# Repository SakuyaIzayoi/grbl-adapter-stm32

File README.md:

# grbl-adapter-stm32
GRBL Adapter using an STM32 BluePill

### Stepcraft D600 GRBL Settings
| Setting | Value | Description |
| --- | --- | --- |
| $0 | 50 | Step pulse time |
| $1 | 100 | Step idle delay |
| $2 | 0 | Step pulse invert |
| $3 | 0 | Step direction invert |
| $4 | 1 | Invert step enable pin |
| $5 | 1 | Invert limit pins |
| $6 | 1 | Invert probe pin |
| $10 | 1 | Status report options |
| $11 | 0.010 | Junction deviation |
| $13 | 0 | Report in inches |
| $20 | 1 | Soft limits enable |
| $21 | 1 | Hard limits enable |
| $22 | 1 | Homing cycle enable |
| $23 | 1 | Homing direction invert |
| $24 | 120.000 | Homing locate feed rate |
| $25 | 900.000 | Homing search seek rate |
| $26 | 250 | Homing switch debounce delay |
| $27 | 1.000 | Homing switch pull-off distance |
| $30 | 1000 | Maximum spindle speed |
| $31 | 0 | Minimum spindle speed |
| $32 | 0 | Laser-mode enable |
| $100 | 133.333 | X-ais travel resolution |
| $101 | 133.333 | Y-ais travel resolution |
| $102 | 133.333 | Z-ais travel resolution |
| $103 | 133.333 | A-ais travel resolution |
| $110 | 800.000 | X-axis maximum rate |
| $111 | 800.000 | Y-axis maximum rate |
| $112 | 800.000 | Z-axis maximum rate |
| $113 | 800.000 | A-axis maximum rate |
| $120 | 5.000 | X-axis acceleration |
| $121 | 5.000 | Y-axis acceleration |
| $122 | 5.000 | Z-axis acceleration |
| $123 | 5.000 | A-axis acceleration |
| $130 | 300.000 | X-axis maximum travel |
| $131 | 420.000 | Y-axis maximum travel |
| $132 | 140.000 | Z-axis maximum travel |
| $133 | 100.000 | A-axis maximum travel |

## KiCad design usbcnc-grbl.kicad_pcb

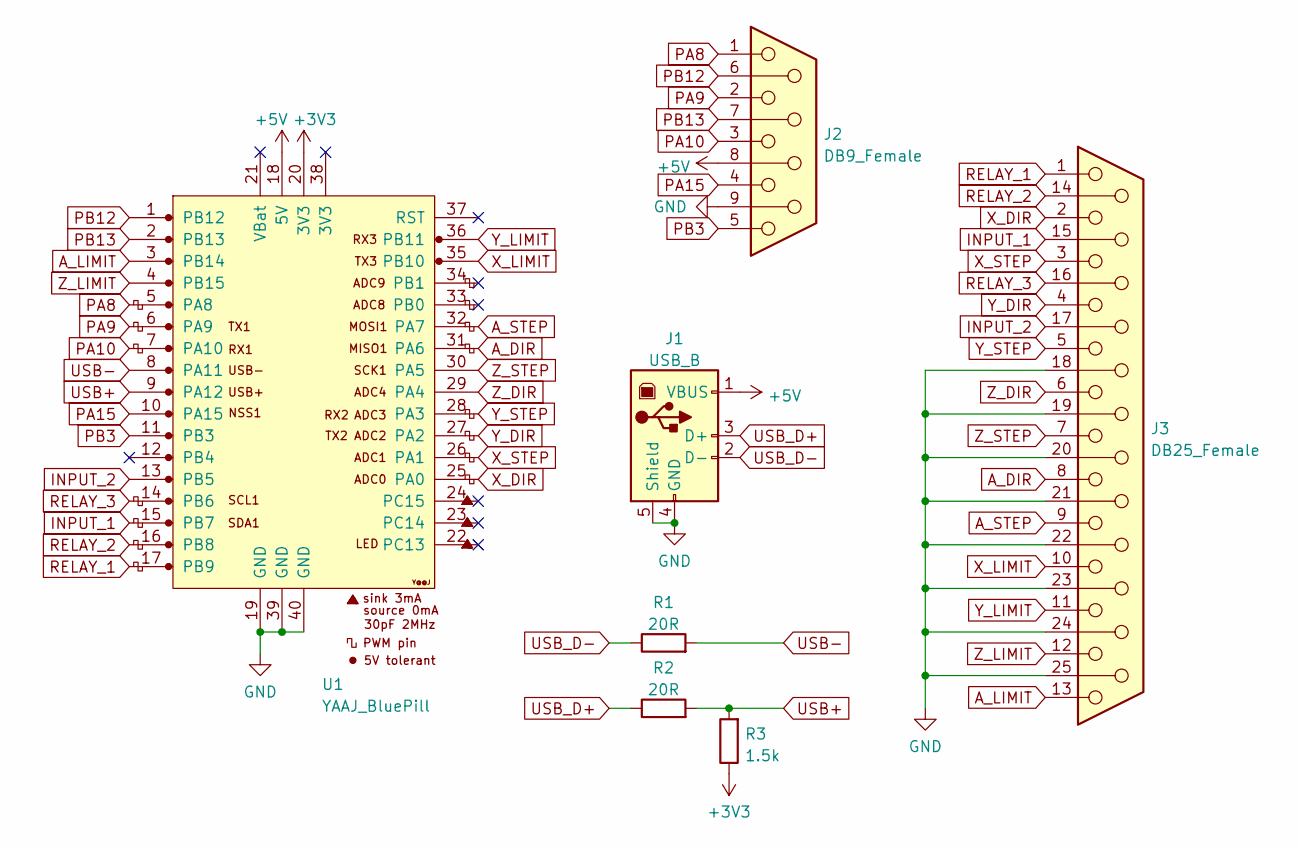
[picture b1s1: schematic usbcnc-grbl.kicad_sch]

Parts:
J1: USB_B; USB_B_OST_USB-B1HSxx_Horizontal
J2: DB9_Female; DSUB-9_Female_EdgeMount_P2.77mm
J3: DB25_Female; DSUB-25_Female_EdgeMount_P2.77mm
R1, R2: 20R; R_0805_2012Metric_Pad1.20x1.40mm_HandSolder
R3: 1.5k; R_0805_2012Metric_Pad1.20x1.40mm_HandSolder
U1: YAAJ_BluePill; YAAJ_BluePill_2

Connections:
+3V3: R3.1, U1.20 (3V3)
+5V: J1.1 (VBUS), J2.8, U1.18 (5V)
A_DIR: J3.8, U1.31 (PA6)
A_LIMIT: J3.13, U1.3 (PB14)
A_STEP: J3.9, U1.32 (PA7)
GND: J1.4 (GND), J1.5 (Shield), J2.9, J3.18, J3.19, J3.20, J3.21, J3.22, J3.23, J3.24, J3.25, U1.19 (GND), U1.39 (GND), U1.40 (GND)
INPUT_1: J3.15, U1.15 (PB7)
INPUT_2: J3.17, U1.13 (PB5)
PA8: J2.1, U1.5 (PA8)
PA9: J2.2, U1.6 (PA9)
PA10: J2.3, U1.7 (PA10)
PA15: J2.4, U1.10 (PA15)
PB3: J2.5, U1.11 (PB3)
PB12: J2.6, U1.1 (PB12)
PB13: J2.7, U1.2 (PB13)
RELAY_1: J3.1, U1.17 (PB9)
RELAY_2: J3.14, U1.16 (PB8)
RELAY_3: J3.16, U1.14 (PB6)
USB+: R2.2, R3.2, U1.9 (PA12)
USB-: R1.2, U1.8 (PA11)
USB_D+: J1.3 (D+), R2.1
USB_D-: J1.2 (D-), R1.1
X_DIR: J3.2, U1.25 (PA0)
X_LIMIT: J3.10, U1.35 (PB10)
X_STEP: J3.3, U1.26 (PA1)
Y_DIR: J3.4, U1.27 (PA2)
Y_LIMIT: J3.11, U1.36 (PB11)
Y_STEP: J3.5, U1.28 (PA3)
Z_DIR: J3.6, U1.29 (PA4)
Z_LIMIT: J3.12, U1.4 (PB15)
Z_STEP: J3.7, U1.30 (PA5)

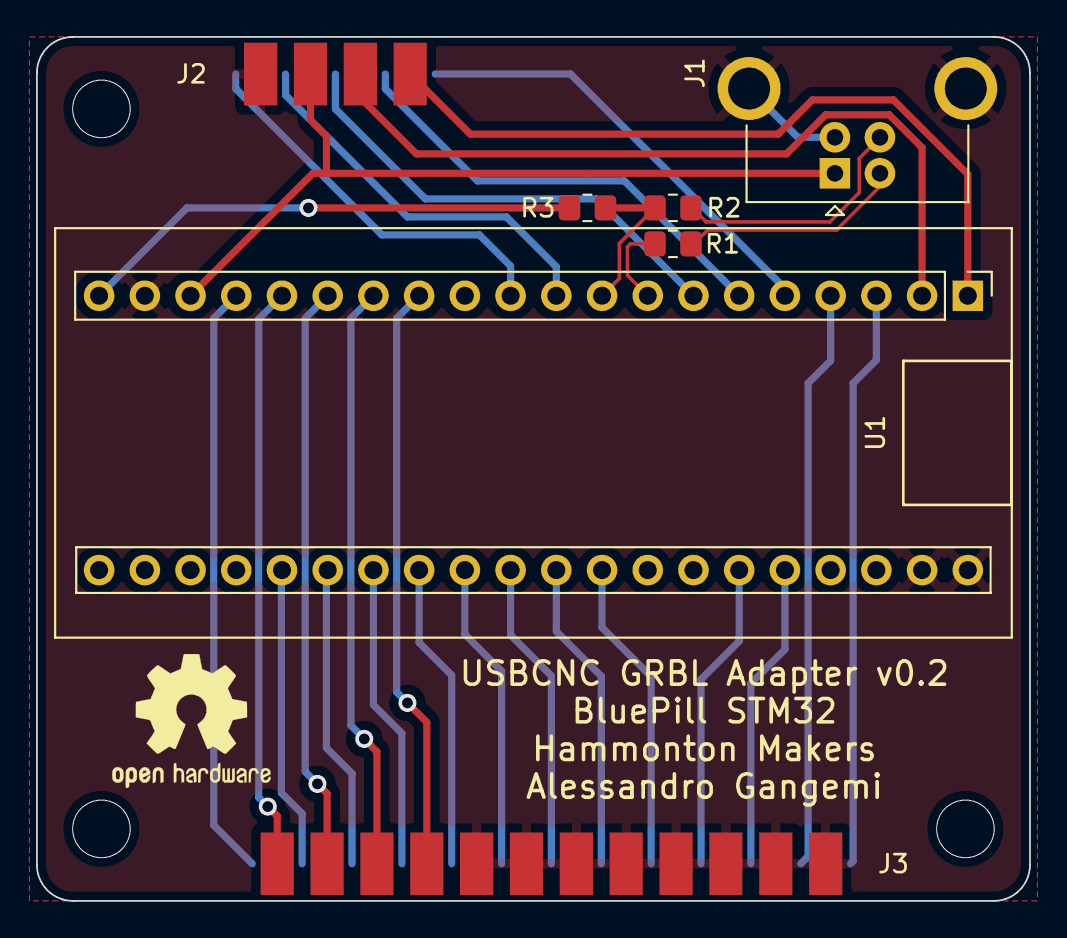
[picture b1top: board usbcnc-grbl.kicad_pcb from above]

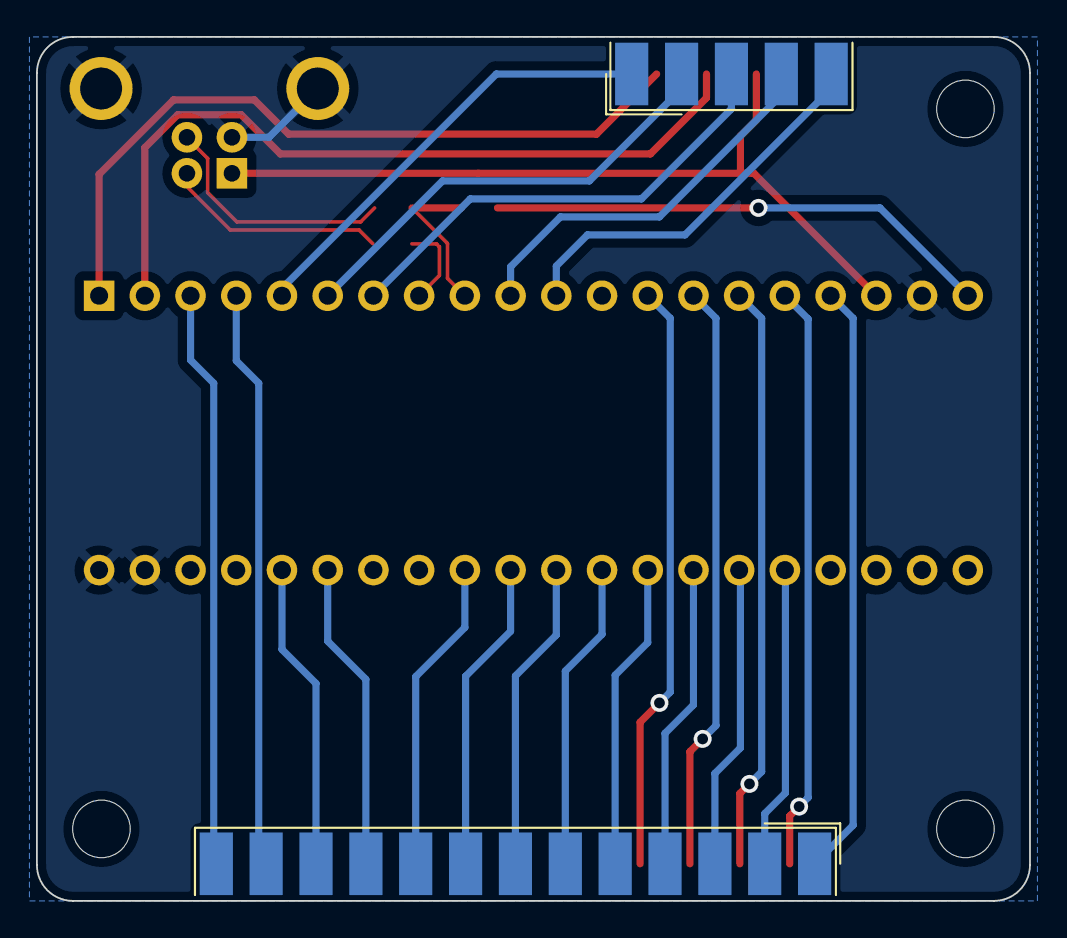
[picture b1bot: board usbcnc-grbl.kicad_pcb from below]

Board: 2 copper layers, 55.2 x 48.0 mm, 7 parts (2 on the bottom side), 31 nets.

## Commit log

2023-05-27 Initial commit
    Version 0.2 with USB resistors
2023-05-27 Fix pullup on USB
2023-06-10 Update README.md
    Enable soft limits
2023-06-11 Update to Kicad 7
